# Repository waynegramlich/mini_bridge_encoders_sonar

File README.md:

# mini_bridge_encoders_sonar

The Bridge/Encoders/Sonar Mini-Shield is a
[Busino](https://github.com/waynegramlich/busino)
compatible mini-shield.  It provides the ability
to connectxyzo to:

* 2 small 1A DC motors,

* 2 shaft encoders, and

* 2 Sonar range finders.

The power comes from the motor power bus and is
fully electrically isolated (using opto-isolators)
from the logic bus.

Currently, everything is located in the `rev_a` directory.

## Revision A

The revision A schematic is available as either
`mini_bridge_encoders_sonar.pdf` or as
`mini_bridge_encoders_sonar.svg`.

The is circuit is broken to electrically isolated sections.
The schematic shows the electrical isolation boundary.

### Logic Side

Logic ground comes in on N2 (pins 5 and 6).  5 Volts
comes in on N2 (pin 3.)  5 volts and ground are routed
to the two shaft encoder connectors N3 and N4 as well
as the two sonar connectors N7 and N8.

The first shaft encoder connects the A and B quadrature
signals to  D5 and D6 on N1.  The second shaft encoder
connects the A and B  quadrature signals to D4 and D2.

{more goes here.}

### Programming

<Table Border="1">
  <TR>
    <TH>Arduino Pin</TH>
    <TH>Function</TH>
  </TR>
  <TR>
    <TD>D0</TD>
    <TD>No Connection</TD>
  </TR>
  <TR>
    <TD>D1</TD>
    <TD>No Connection</TD>
  </TR>
  <TR>
    <TD>D2</TD>
    <TD>Encoder N4-2 Phase A</TD>
  </TR>
  <TR>
    <TD>D3</TD>
    <TD>Sonar N8-3 Trigger</TD>
  </TR>
  <TR>
    <TD>D4</TD>
    <TD>Encoder N4-3 Phase B</TD>
  </TR>
  <TR>
    <TD>D5</TD>
    <TD>Encoder N3-2 Phase A</TD>
  </TR>
  <TR>
    <TD>D6</TD>
    <TD>Encoder N3-3 Phase B</TD>
  </TR>
  <TR>
    <TD>D7</TD>
    <TD>H-Bridge 4A</TD>
  </TR>
  <TR>
    <TD>D8</TD>
    <TD>H-Bridge 3A</TD>
  </TR>
  <TR>
    <TD>D9</TD>
    <TD>Sonar N7-3 Trigger</TD>
  </TR>
  <TR>
    <TD>D10</TD>
    <TD>H-Bridge 3/4 Enable</TD>
  </TR>
  <TR>
    <TD>D11</TD>
    <TD>H-Bridge 1/2 Enable</TD>
  </TR>
  <TR>
    <TD>D12</TD>
    <TD>H-Bridge 2A</TD>
  </TR>
  <TR>
    <TD>D13</TD>
    <TD>H-Bridge 1A</TD>
  </TR>
  <TR>
    <TD>A0</TD>
    <TD>Sonar N8-2 Echo Return</TD>
  </TR>
  <TR>
    <TD>A1</TD>
    <TD>Sonar N7-2 Echo Return</TD>
  </TR>
  <TR>
    <TD>A2</TD>
    <TD>No Connection</TD>
  </TR>
  <TR>
    <TD>A3</TD>
    <TD>No Connection</TD>
  </TR>
  <TR>
    <TD>A4</TD>
    <TD>No Connection</TD>
  </TR>
  <TR>
    <TD>A5</TD>
    <TD>No Connection</TD>
  </TR>
</Table>

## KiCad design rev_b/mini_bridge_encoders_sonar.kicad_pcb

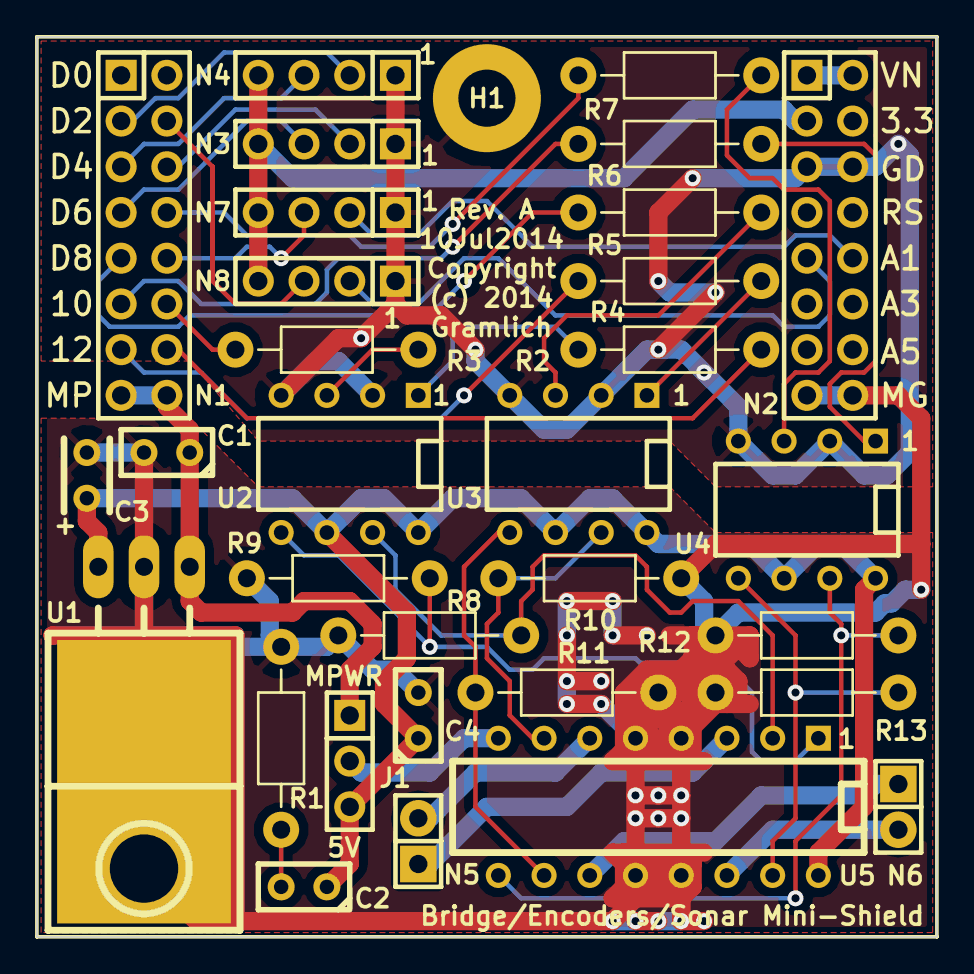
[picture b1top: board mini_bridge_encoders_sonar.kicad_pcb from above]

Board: 2 copper layers, 50.0 x 50.0 mm, 33 parts (1 on the bottom side), 38 nets.

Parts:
C1: 22uF; Capacitor3MMDiscRM2.5
C2, C4: .1uF; Capacitor3MMDiscRM2.5
C3: 22uF; Capacitor4x3RM2-5_RevB
G1: OSHW_LOGO; OSHW_LOGO_400mil
H1: 3MM_HOLE; MountingHole_3mm
J1: POWER_SELECT; Pin_Header_Straight_1x03
N1: MS_DATA_HEADER; Pin_Header_Straight_2x08
N2: MS_PWR_HEADER; Pin_Header_Straight_2x08
N3, N4: ENCODER_CONNECTOR; Pin_Header_Straight_1x04
N5, N6: MOTOR_CONNECTOR; Pin_Header_Straight_1x02
N7, N8: HC_SR04_CONNECTOR; Pin_Header_Straight_1x04
R1: .47; Resistor_Horizontal_400
R2, R3, R4, R5, R6, R7: 470; Resistor_Horizontal_400
R8, R9, R10, R11, R12, R13: 10K; Resistor_Horizontal_400
U1: LM2940; TO-220_Neutral123_Horizontal_LargePads
U2, U3, U4: LTV-826; DIP-8__300
U5: 754410; DIP-16__300

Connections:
/5V: N2.3, N3.4, N4.4, N7.4, N8.4
/A0: N2.9, N8.2
/A1: N2.10, N7.2
/D2: N1.3, N4.2
/D3: N1.4, N8.3
/D4: N1.5, N4.3
/D5: N1.6, N3.2
/D6: N1.7, N3.3
/D7: N1.8, R7.1
/D8: N1.9, R5.1
/D9: N1.10, N7.3
/D10: N1.11, R6.1
/D11: N1.12, R3.1
/D12: N1.13, R4.1
/D13: N1.14, R2.1
/M1+: N5.1, U5.3
/M1-: N5.2, U5.6
/M2+: N6.1, U5.11
/M2-: N6.2, U5.14
/M5V: C2.1, C3.1, C4.1, J1.3, U1.3, U2.6, U2.8, U3.6, U3.8, U4.6, U4.8, U5.16
/MGND: C1.2, C3.2, C4.2, N2.15, N2.16, R1.1, R8.1, R9.1, R10.1, R11.1, R12.1, R13.1, U1.2, U5.4, U5.5, U5.12, U5.13
/MOTOR_POWER: J1.2, U5.8
/MPWR: C1.1, J1.1, N1.15, N1.16, U1.1
/VIN: N2.1, N2.2
GND: H1.1, N2.5, N2.6, N3.1, N4.1, N7.1, N8.1, U2.2, U2.4, U3.2, U3.4, U4.2, U4.4
unnamed: C2.2, R1.2
unnamed: R2.2, U2.1
unnamed: R3.2, U2.3
unnamed: R4.2, U3.1
unnamed: R5.2, U3.3
unnamed: R6.2, U4.1
unnamed: R7.2, U4.3
unnamed: R8.2, U2.7, U5.2
unnamed: R9.2, U2.5, U5.1
unnamed: R10.2, U3.7, U5.7
unnamed: R11.2, U3.5, U5.10
unnamed: R12.2, U4.7, U5.9
unnamed: R13.2, U4.5, U5.15

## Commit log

2014-06-25 Made of copy of mini_template.
2014-06-30 Initial schematic complete.
2014-07-03 Initial layout is complete.
2014-07-10 Got Revision A in pretty good shape.
2014-07-11 Layed out board again (Rev. B) with separate GND and MGND zones. The electrical isolation is also physical isolation.
2014-07-13 Added Edge Cuts.
2014-07-14 Dealt with some more PCB edge incursions.
2014-08-13 Added some more documentation.
2014-08-13 Fixed some table typos

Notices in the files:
rev_b/mini_bridge_encoders_sonar.kicad_pcb:
(c) 2014
